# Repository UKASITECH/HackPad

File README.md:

# Hackpad

built by Umang Kumar Singh for HackClub 2026

Hackpad is my first crack at a hardware project — a simple macropad with seven keys and a rotary encoder. Seven keys for whatever macros you want (calculator hotkey, anyone?), and the encoder handles volume or media scrubbing.

The body is two 3D-printed shells held together with M3 screws and heat-set inserts, with a translucent acrylic plate sandwiched in between. The plate can be swapped out pretty easily if you ever want to change the look.

Under the hood it runs QMK with two layers — a mix of keys I don't have easy access to on my main keyboard, plus a few keycodes I thought were amusing. The 128x32 OLED scrolls through *very important and relevant* information on loop.

Overall this was a blast. I'd never done PCB design before, and learning KiCad from scratch was surprisingly rewarding. The case was straightforward in CAD, and working around the PCB constraints made for a fun little puzzle. Firmware was the biggest headache, but after digging through QMK and XIAO docs for a while things started clicking. Once the parts arrived, assembly was smooth — I only had to reprint the case once.

9/10. Would build again.

## PCB

# Bill of materials
- 7x Cherry MX-style keyswitches.
- 4x M3x12mm screws
- 4x M3 X D4.6 X L3.6
- 8x 1N4148 Diodes (through hole)
- 1x EC11 Rotary encoder
- 1x 0.91 inch SSD1306 OLED
- 14x Mill-Max 3305s or 0305s.

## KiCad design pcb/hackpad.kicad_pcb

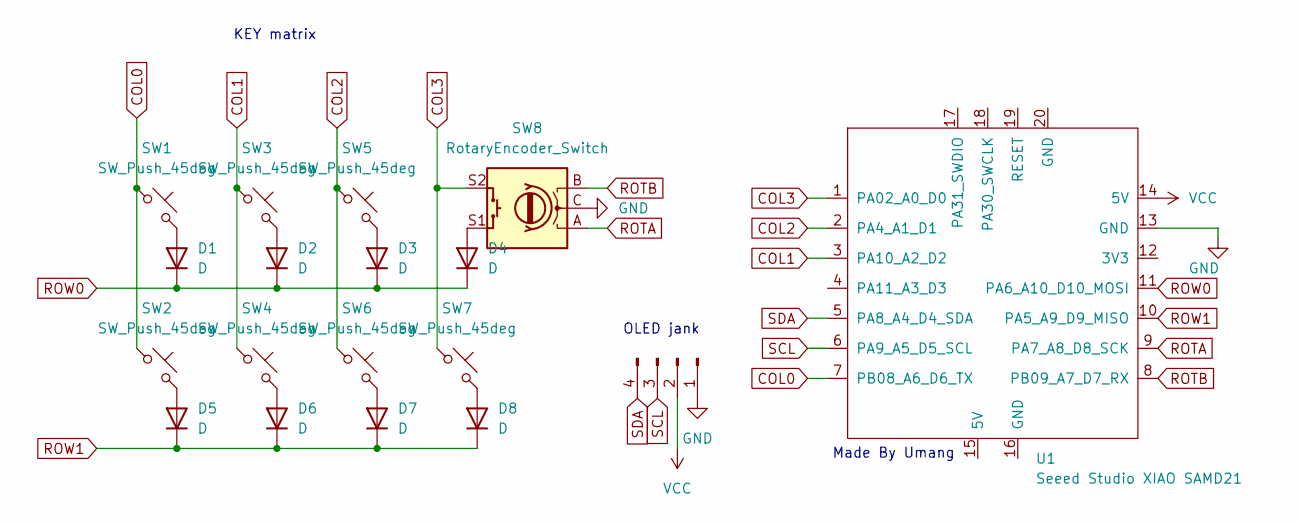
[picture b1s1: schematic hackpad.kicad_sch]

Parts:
D1, D2, D3, D4, D5, D6, D7, D8: D; D_DO-35_SOD27_P7.62mm_Horizontal
O1: OLEd; SSD1306-0.91-OLED-4pin-128x32
SW1, SW2, SW3, SW4, SW5, SW6, SW7: SW_Push_45deg; SW_Cherry_MX_1.00u_PCB
SW8: RotaryEncoder_Switch; RotaryEncoder_Alps_EC11E-Switch_Vertical_H20mm
U1: Seeed Studio XIAO SAMD21; XIAO-Generic-Thruhole-14P-2.54-21X17.8MM

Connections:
COL0: SW1.1, SW2.1, U1.7 (PB08_A6_D6_TX)
COL1: SW3.1, SW4.1, U1.3 (PA10_A2_D2)
COL2: SW5.1, SW6.1, U1.2 (PA4_A1_D1)
COL3: SW7.1, SW8.S2, U1.1 (PA02_A0_D0)
GND: O1.1, SW8.C, U1.13 (GND)
unnamed: D1.2 (A), SW1.2
unnamed: D2.2 (A), SW3.2
unnamed: D3.2 (A), SW5.2
unnamed: D4.2 (A), SW8.S1
unnamed: D5.2 (A), SW2.2
unnamed: D6.2 (A), SW4.2
unnamed: D7.2 (A), SW6.2
unnamed: D8.2 (A), SW7.2
ROTA: SW8.A, U1.9 (PA7_A8_D8_SCK)
ROTB: SW8.B, U1.8 (PB09_A7_D7_RX)
ROW0: D1.1 (K), D2.1 (K), D3.1 (K), D4.1 (K), U1.11 (PA6_A10_D10_MOSI)
ROW1: D5.1 (K), D6.1 (K), D7.1 (K), D8.1 (K), U1.10 (PA5_A9_D9_MISO)
SCL: O1.3, U1.6 (PA9_A5_D5_SCL)
SDA: O1.4, U1.5 (PA8_A4_D4_SDA)
VCC: O1.2, U1.14 (5V)

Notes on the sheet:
Made By Umang
OLED jank
KEY matrix

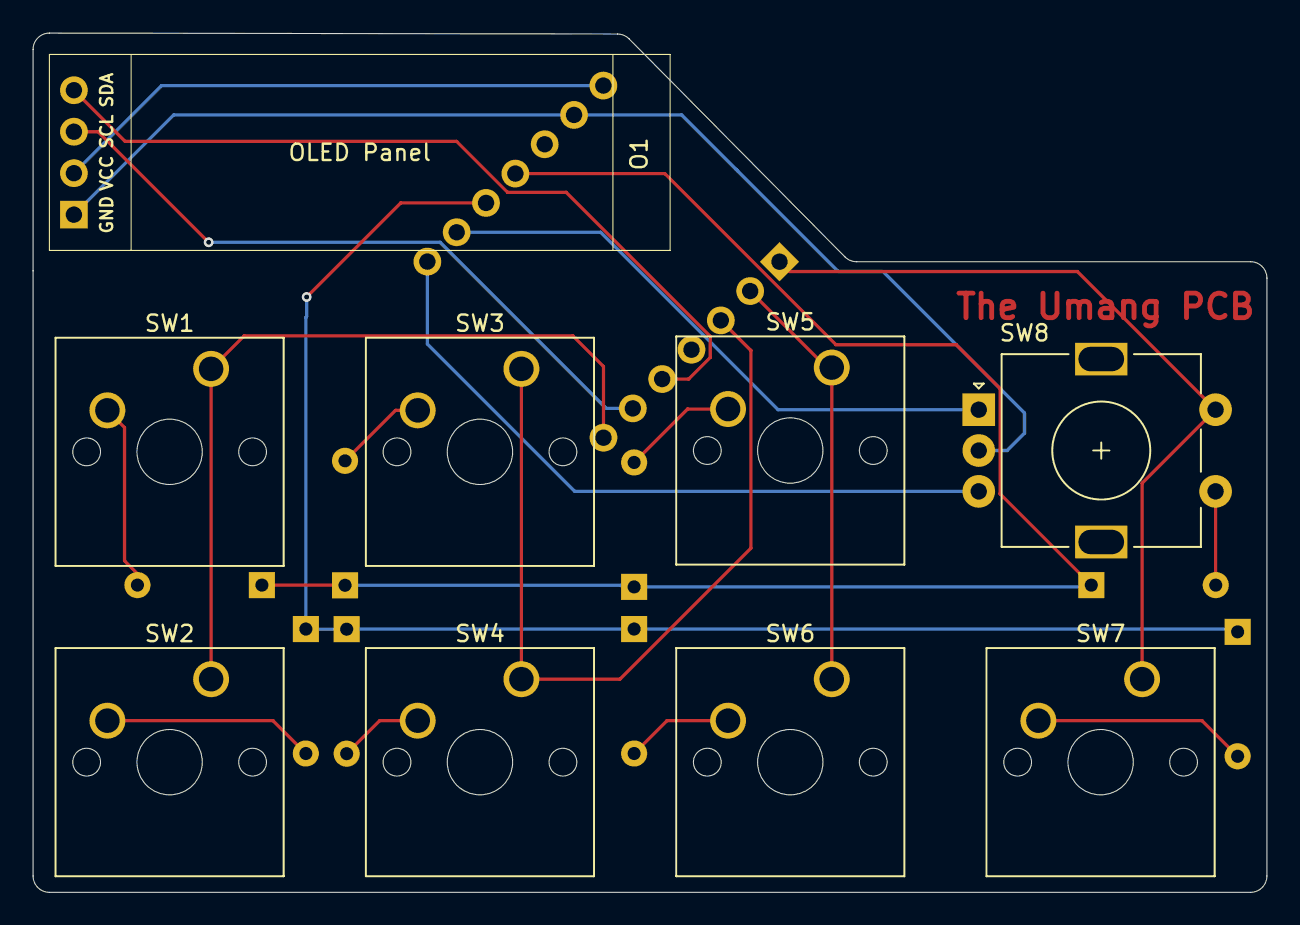
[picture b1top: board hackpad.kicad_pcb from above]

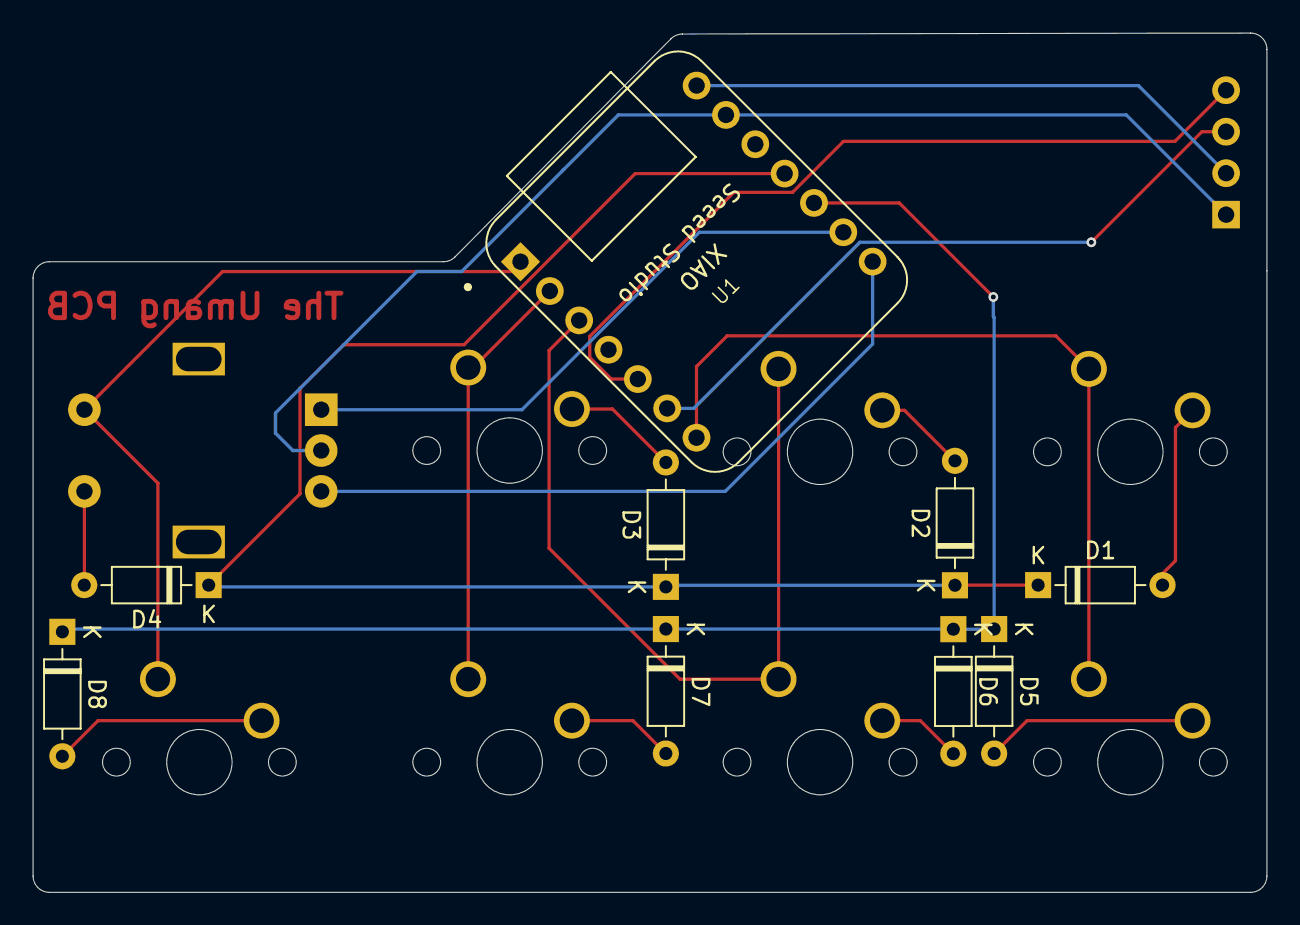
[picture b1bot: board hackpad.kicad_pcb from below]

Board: 2 copper layers, 75.5 x 52.6 mm, 18 parts (9 on the bottom side), 20 nets.

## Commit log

2026-06-08 Initial commit - Hackpad macropad
